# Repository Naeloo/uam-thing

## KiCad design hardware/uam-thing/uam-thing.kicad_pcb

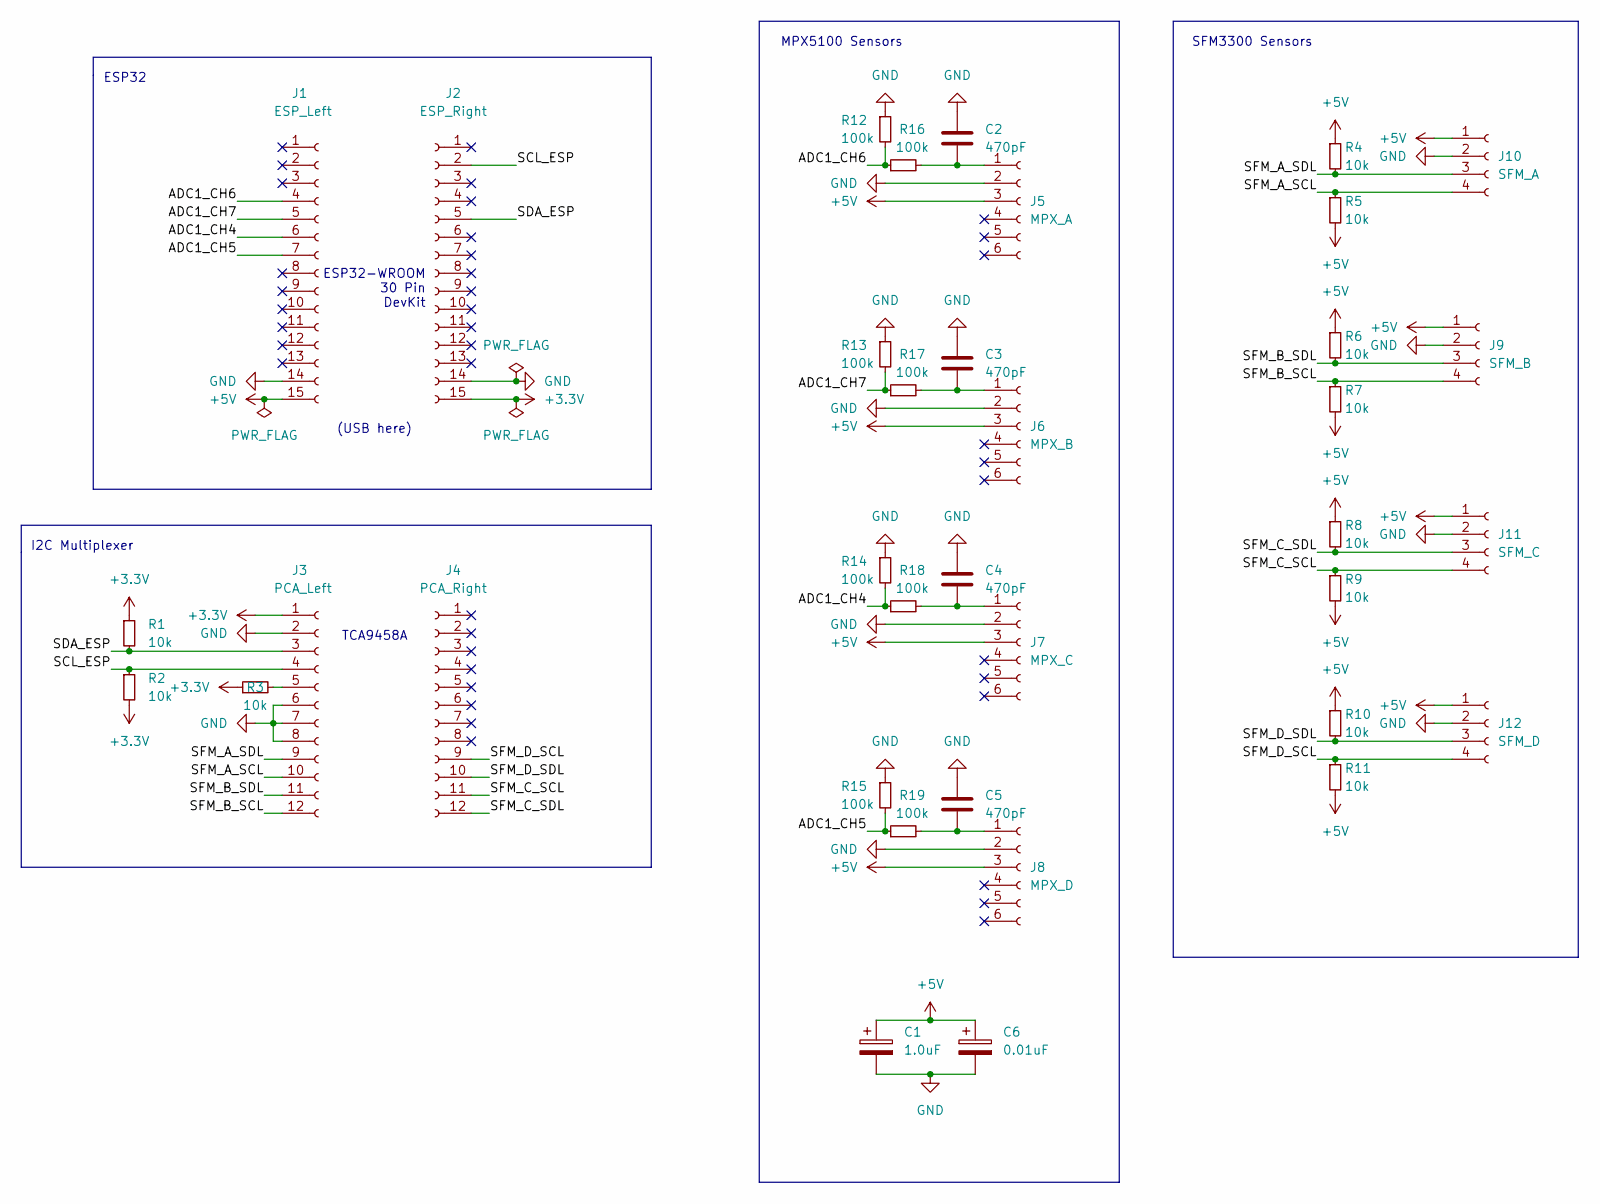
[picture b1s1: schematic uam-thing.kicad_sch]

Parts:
C1: 1.0uF; CP_Radial_D5.0mm_P2.00mm
C2, C3, C4, C5: 470pF; C_Disc_D4.7mm_W2.5mm_P5.00mm
C6: 0.01uF; C_Disc_D4.7mm_W2.5mm_P5.00mm
J1: ESP_Left; PinHeader_1x15_P2.54mm_Vertical
J2: ESP_Right; PinHeader_1x15_P2.54mm_Vertical
J3: PCA_Left; PinHeader_1x12_P2.54mm_Vertical
J4: PCA_Right; PinHeader_1x12_P2.54mm_Vertical
J5: MPX_A; PinHeader_1x06_P2.54mm_Vertical
J6: MPX_B; PinHeader_1x06_P2.54mm_Vertical
J7: MPX_C; PinHeader_1x06_P2.54mm_Vertical
J8: MPX_D; PinHeader_1x06_P2.54mm_Vertical
J9: SFM_B; JST_XH_B4B-XH-A_1x04_P2.50mm_Vertical
J10: SFM_A; JST_XH_B4B-XH-A_1x04_P2.50mm_Vertical
J11: SFM_C; JST_XH_B4B-XH-A_1x04_P2.50mm_Vertical
J12: SFM_D; JST_XH_B4B-XH-A_1x04_P2.50mm_Vertical
R1, R2, R3, R4, R5, R6, R7, R8, R9, R10, R11: 10k; R_Axial_DIN0207_L6.3mm_D2.5mm_P10.16mm_Horizontal
R12, R13, R14, R15, R16, R17, R18, R19: 100k; R_Axial_DIN0207_L6.3mm_D2.5mm_P10.16mm_Horizontal

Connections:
+3.3V: J2.15, J3.1, R1.1, R2.2, R3.1
+5V: C1.1, C6.1, J1.15, J5.3, J6.3, J7.3, J8.3, J9.1, J10.1, J11.1, J12.1, R4.1, R5.2, R6.1, R7.2, R8.1, R9.2, R10.1, R11.2
/ADC1_CH4: J1.6, R14.2, R18.1
/ADC1_CH5: J1.7, R15.2, R19.1
/ADC1_CH6: J1.4, R12.2, R16.1
/ADC1_CH7: J1.5, R13.2, R17.1
/SCL_ESP: J2.2, J3.4, R2.1
/SDA_ESP: J2.5, J3.3, R1.2
/SFM_A_SCL: J3.10, J10.4, R5.1
/SFM_A_SDL: J3.9, J10.3, R4.2
/SFM_B_SCL: J3.12, J9.4, R7.1
/SFM_B_SDL: J3.11, J9.3, R6.2
/SFM_C_SCL: J4.11, J11.4, R9.1
/SFM_C_SDL: J4.12, J11.3, R8.2
/SFM_D_SCL: J4.9, J12.4, R11.1
/SFM_D_SDL: J4.10, J12.3, R10.2
GND: C1.2, C2.1, C3.1, C4.1, C5.1, C6.2, J1.14, J2.14, J3.2, J3.6, J3.7, J3.8, J5.2, J6.2, J7.2, J8.2, J9.2, J10.2, J11.2, J12.2, R12.1, R13.1, R14.1, R15.1
unnamed: C2.2, J5.1, R16.2
unnamed: C3.2, J6.1, R17.2
unnamed: C4.2, J7.1, R18.2
unnamed: C5.2, J8.1, R19.2
unnamed: J3.5, R3.2

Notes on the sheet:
I2C Multiplexer
SFM3300 Sensors
MPX5100 Sensors
ESP32
(USB here)
TCA9458A
ESP32-WROOM 30 Pin DevKit

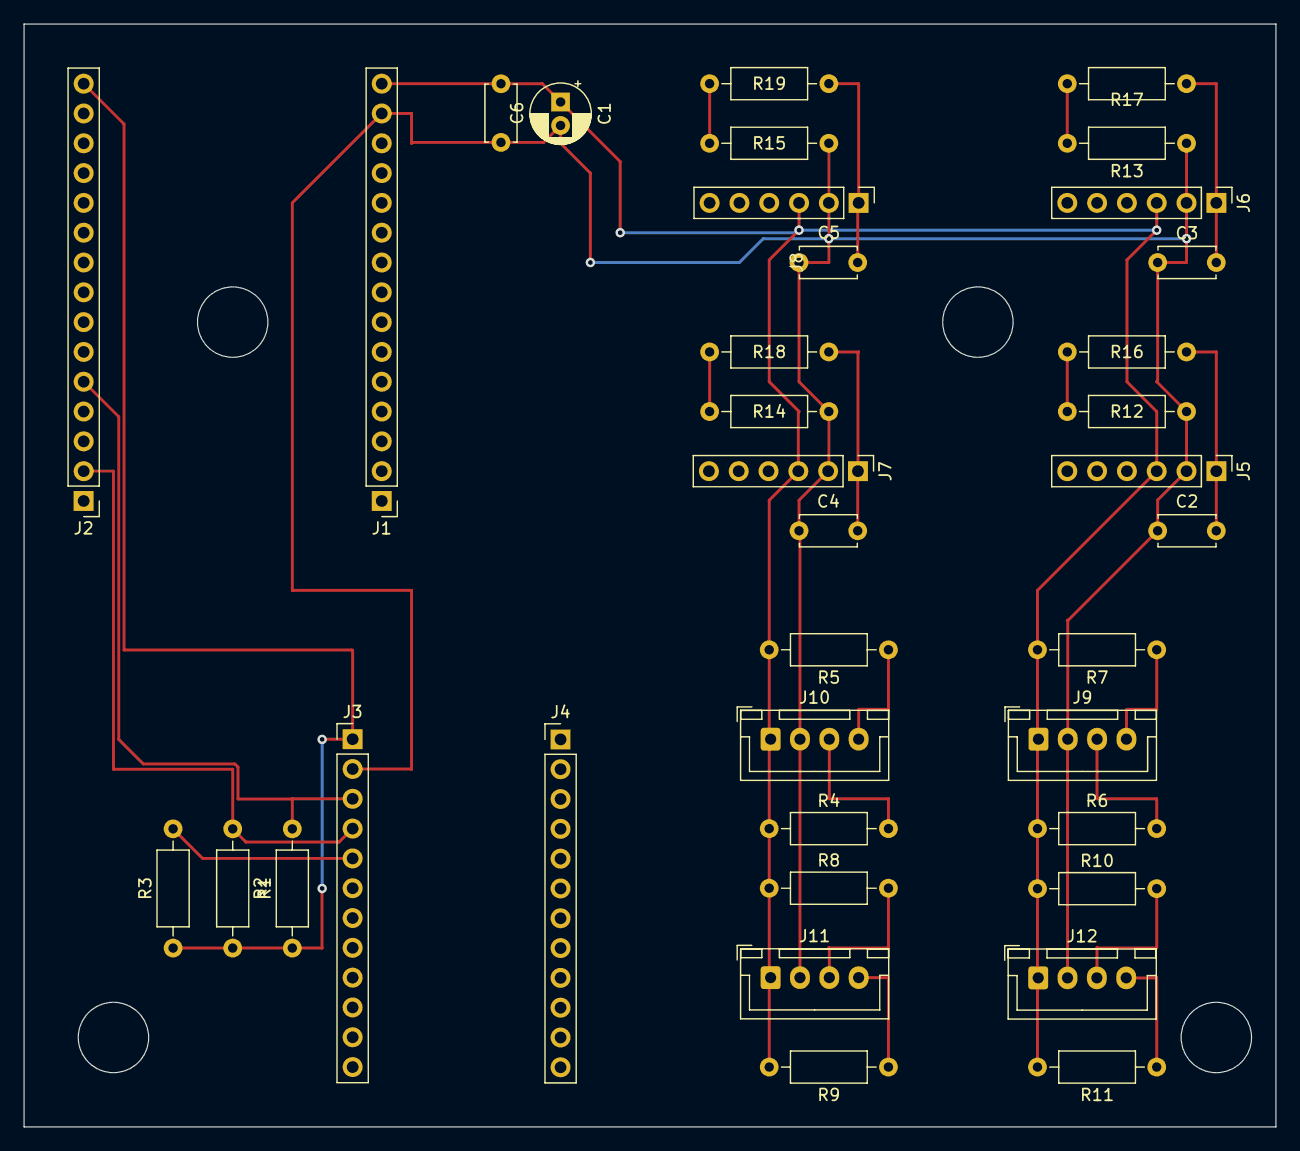
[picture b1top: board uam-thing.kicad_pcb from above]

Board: 2 copper layers, 106.7 x 94.0 mm, 37 parts (0 on the bottom side), 22 nets.

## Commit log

2022-08-22 Basic networking and MQTT
2022-08-22 Analog data via MQTT
2022-08-22 Preliminary KiCad sketches
2022-08-28 First version of hardware design
2022-08-29 Voltage dividers for MPX sensors
2022-08-30 Basic flow sensor code
2022-08-30 ADC channel 6 for pressure sensor p1
2022-09-05 Reworked PCB for 4 pin JST, replaced connectors again
2022-09-05 Space saving PCB, now fits 100x100
2022-09-13 Updated header footprints
2022-09-13 Flow sensor identification
2022-09-16 Reorganized 5V and GND lines
2022-09-16 SFM CRC error checking
2022-09-16 Handle SFM read error states
2022-09-17 Some final hardware revisions
2022-09-19 SFM communication finished
2022-09-19 Final V1 board revision and case
2022-09-19 Ignore KiCad backups
